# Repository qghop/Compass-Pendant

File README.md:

# Compass-Pendant
WIP - Creating a Pendant with LEDs and a Compass Module on a custom PCB

## Design Goals and Inspiration

The main design goal from the beginning was to create a unique piece of jewlery, from a Custom PCB with real-world functional components. 

Several purposes were ideated for this purpose. I initially wanted to create a GPS Logging Device to track my position, an idea I was first enamored by with [BOTW's Hero's Path Mode](https://www.youtube.com/watch?v=YSooSC6LfSU), and without giving my position data away to, or relying upon, a huge company like Google Maps' Timeline feature requires. I couldn't figure out a way to keep all the components small for this idea, so it was shelved, though I implemented a similar feature in my [Apple Photos Analysis Project](https://github.com/qghop/Apple-Photos-Analysis).

Different sensors, chips, and general designs were considered, but eventually using a Coin Cell Battery, an ATmega328P, and an I2C Magnetometer were chosen for ease of implementing, in both wiring and programming. 

The whole project was heavily inspired by the work of [Mitxela](https://mitxela.com/), especially his [UV Protection Amulet](https://www.youtube.com/watch?v=JhNMeJZ8Ll0) and [Fluid Simulation Pendant](https://www.youtube.com/watch?v=jis1MC5Tm8k). The header for chip programming was taken from the [KeyChainino](https://www.keychainino.com/) project, thanks to [upir](https://www.youtube.com/watch?v=Zsum_6dWfVU) for their video on the device. Additional thanks to the hundreds of KiCad tutorials used to build the PCB.

## Media

### V1

## V1 Successes

Honestly, I was suprised by how not difficult this project was. Obviously I have a very basic scope, but to have my PCB design work, essentially, first try, is remarkable as someone with only the base electrical experience required of a Mechanical Engineering grad. KiCad especially proved to be quite easy to learn.

A functional V1 device was created!

## V1 Failures

- A switch was initially considered, but was removed to more easily wire connections with the large battery pads taking most of the limited space. This was a mistake, a switch is really required for actual use. Removing the battery from the chosen holder is not easy, and a case for the PCB (which could hide the LEDs) would add a ton of complexity, and would cover up an, in my opinion, great looking bare PCB.

- The battery is oddly inconsistent in delivering power to the magnetometer. This problem needs to be properly diagnosed, but there is no issue in running the debug "BasicSpinningLights.ino" sketch, but there is sometimes issues with the Compass program loaded.

- PCBA is too expensive to justify for revisions, so V2 should be designed so I could assemble myself (mostly meaning larger components).

- The small, red LEDs aren't as appealing as envisioned. Could be fixed with a diffuser, a larger or variable resistor, or a cooler (blue, green) color.

- The snap-off header could be designed to be easier to cut off, or designed to be integrated into the jewlery, as say the part that connects to the necklace chain.

## Programming

I primarily referenced the [KeyChainino Guide](https://www.keychainino.com/how-to-program-keychainino-v144-via-isp/) for programming. Below is a summarized version, with some tweaks.

1. Install the MiniCore Library to the Arduino IDE.

2. Load the example sketch "ArduinoISP" to the Arduino UNO.

3. Remove the battery from the Pendant, and don't put it back in until finished. Physically connect the Pendant programming header to the proper pins of the UNO. 

    This can be done via wiring:

    Or via the ISP header of the UNO. The RESET pin of the ISP pins cannot be used though, so there must still be one manual connection to Digital Pin 10, acting as a digital reset:

4. Switch to the ATmega328 Board, with the following settings:

5. If first time programming the chip, run "Burn Bootloader" from Tools

6. Upload the sketch. If errors occour, wires are likely not connected properly. Tilting the pendant or the wires can help ensure connection.

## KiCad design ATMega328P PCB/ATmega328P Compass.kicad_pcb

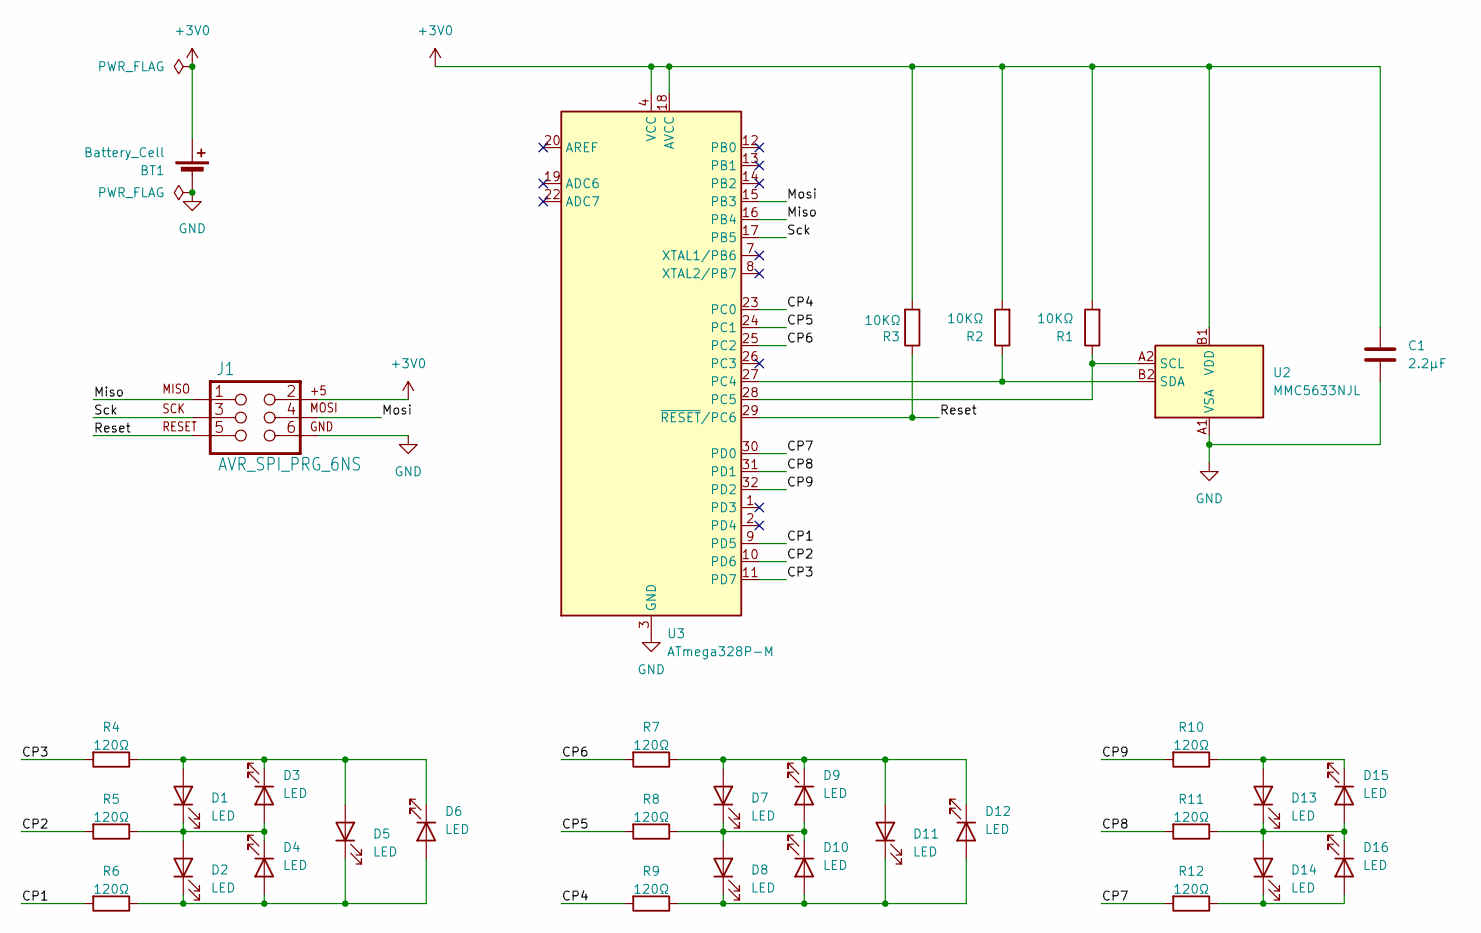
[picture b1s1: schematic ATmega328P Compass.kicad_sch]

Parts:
BT1: Battery_Cell; BatteryHolder_Keystone_3034_1x20mm
C1: 2.2µF; C_01005_0402Metric_Pad0.57x0.30mm_HandSolder
D1, D2, D3, D4, D5, D6, D7, D8, D9, D10, D11, D12, D13, D14, D15, D16: LED; LED_01005_0402Metric_Pad0.57x0.30mm_HandSolder
J1: AVR_SPI_PRG_6NS; 2X3-NS
R1, R2, R3: 10KΩ; R_0402_1005Metric_Pad0.72x0.64mm_HandSolder
R4, R5, R6, R7, R8, R9, R10, R11, R12: 120Ω; R_0402_1005Metric_Pad0.72x0.64mm_HandSolder
U2: MMC5633NJL; WLP-4_0.86x0.86mm_P0.4mm
U3: ATmega328P-M; QFN-32-1EP_5x5mm_P0.5mm_EP3.1x3.1mm

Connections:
+3V0: BT1.1 (+), C1.1, J1.2, R1.2, R2.2, R3.2, U2.B1 (VDD), U3.4 (VCC), U3.6 (VCC), U3.18 (AVCC)
/CP1: R6.2, U3.9 (PD5)
/CP2: R5.2, U3.10 (PD6)
/CP3: R4.2, U3.11 (PD7)
/CP4: R9.2, U3.23 (PC0)
/CP5: R8.2, U3.24 (PC1)
/CP6: R7.2, U3.25 (PC2)
/CP7: R12.2, U3.30 (PD0)
/CP8: R11.2, U3.31 (PD1)
/CP9: R10.2, U3.32 (PD2)
/Miso: J1.1, U3.16 (PB4)
/Mosi: J1.4, U3.15 (PB3)
/Reset: J1.5, R3.1, U3.29 (~RESET/PC6)
/Sck: J1.3, U3.17 (PB5)
GND: BT1.2 (-), C1.2, J1.6, U2.A1 (VSA), U3.3 (GND), U3.5 (GND), U3.21 (GND), U3.33 (GND)
unnamed: D1.2 (A), D3.1 (K), D5.2 (A), D6.1 (K), R4.1
unnamed: D1.1 (K), D2.2 (A), D3.2 (A), D4.1 (K), R5.1
unnamed: D2.1 (K), D4.2 (A), D5.1 (K), D6.2 (A), R6.1
unnamed: D8.1 (K), D10.2 (A), D11.1 (K), D12.2 (A), R9.1
unnamed: D7.1 (K), D8.2 (A), D9.2 (A), D10.1 (K), R8.1
unnamed: D7.2 (A), D9.1 (K), D11.2 (A), D12.1 (K), R7.1
unnamed: D13.2 (A), D15.1 (K), R10.1
unnamed: D13.1 (K), D14.2 (A), D15.2 (A), D16.1 (K), R11.1
unnamed: D14.1 (K), D16.2 (A), R12.1
unnamed: R1.1, U2.A2 (SCL), U3.28 (PC5)
unnamed: R2.1, U2.B2 (SDA), U3.27 (PC4)

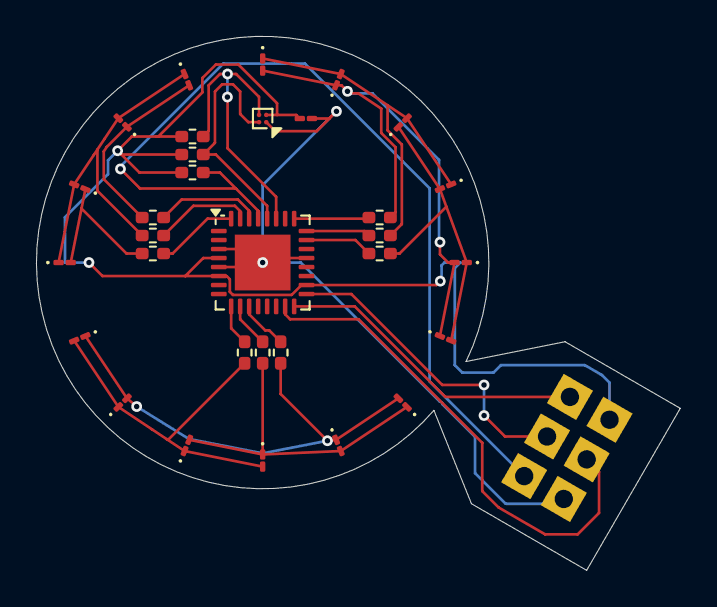
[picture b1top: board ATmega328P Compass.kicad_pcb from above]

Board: 2 copper layers, 35.8 x 29.7 mm, 33 parts (1 on the bottom side), 26 nets.

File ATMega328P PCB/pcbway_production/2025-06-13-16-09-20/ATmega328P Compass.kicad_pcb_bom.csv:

Designator,Quantity,Value,Footprint,Package,MPN,DNP,Mount_Type,Description,Sim.Pins
BT1,1,Battery_Cell,BatteryHolder_Keystone_3034_1x20mm,-,3034TR,,smt,Single-cell battery,
C1,1,2.2µF,C_01005_0402Metric_Pad0.57x0.30mm_HandSolder,0402,CL05A225MQ5NSNC,,smt,Unpolarized capacitor,
"D1, D10, D11, D12, D13, D14, D15, D16, D2, D3, D4, D5, D6, D7, D8, D9",16,LED,LED_01005_0402Metric_Pad0.57x0.30mm_HandSolder,0402,BL-HUB37A-AV-TRB,,smt,Light emitting diode,1=K 2=A
"R1, R2, R3",3,10KΩ,R_0402_1005Metric_Pad0.72x0.64mm_HandSolder,0402,0402WGF1002TCE,,smt,Resistor,
"R10, R11, R12, R4, R5, R6, R7, R8, R9",9,120Ω,R_0402_1005Metric_Pad0.72x0.64mm_HandSolder,0402,0402WGF1200TCE,,smt,Resistor,
U2,1,MMC5633NJL,WLP-4_0.86x0.86mm_P0.4mm,WLP-4(0.9x0.9),MMC5633NJL,,smt,"3-axis AMR Magnetometer, 30 G, I2C & I3C  Interface, 2mG RMS, WLP-4",
U3,1,ATmega328P-M,QFN-32-1EP_5x5mm_P0.5mm_EP3.1x3.1mm,VQFN-32_5x5,ATMEGA328P-MU,,smt,"20MHz, 32kB Flash, 2kB SRAM, 1kB EEPROM, QFN-32",

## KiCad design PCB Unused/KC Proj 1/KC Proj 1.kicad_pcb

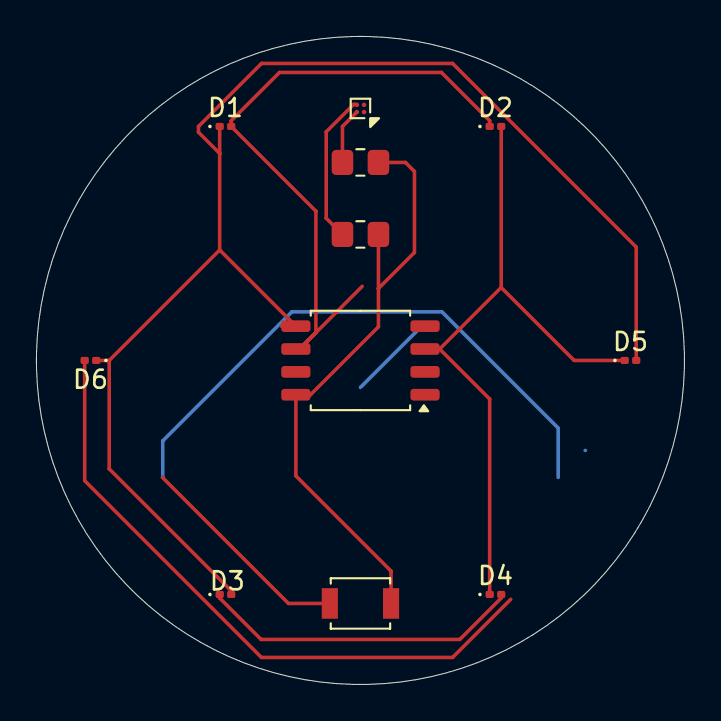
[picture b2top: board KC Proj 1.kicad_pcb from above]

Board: 2 copper layers, 36.0 x 36.0 mm, 12 parts (1 on the bottom side), 8 nets.

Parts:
BT1: Battery_Cell; BatteryHolder_Keystone_3034_1x20mm
D1, D2, D3, D4, D5, D6: LED; LED_0201_0603Metric
R1, R2: 10Kohm; R_0805_2012Metric_Pad1.20x1.40mm_HandSolder
SW1: SW_SPST; SW_SPST_B3U-1000P
U2: MMC5633NJL; WLP-4_0.86x0.86mm_P0.4mm
U3: ATtiny85-20S; SOIC-8_5.3x5.3mm_P1.27mm

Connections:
unnamed: BT1.1 (+), SW1.1 (A)
unnamed: BT1.2 (-), U2.A1 (VSA), U3.4 (GND)
unnamed: D1.2 (A), D2.1 (K), D3.1 (K), D4.2 (A), U3.6 (PB1)
unnamed: D1.1 (K), D3.2 (A), D5.2 (A), D6.1 (K), U3.5 (AREF/PB0)
unnamed: D2.2 (A), D4.1 (K), D5.1 (K), D6.2 (A), U3.3 (XTAL2/PB4)
unnamed: R1.2, R2.2, SW1.2 (B), U2.B1 (VDD), U3.8 (VCC)
unnamed: R1.1, U2.A2 (SCL), U3.7 (PB2)
unnamed: R2.1, U2.B2 (SDA), U3.2 (XTAL1/PB3)

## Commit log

2025-06-14 Uploading PCB 1
    Uploading ATMega328P PCB (First PCB sent to PCBWay) and previous attempts/ideas with ATTiny85+84
2025-06-15 Added v1 Images
2025-07-08 Basic LED control code
2025-07-09 Minor edits for viewing
2025-07-09 Added media, code from working device
2025-07-09 Revamped Readme
2025-07-09 Added videos to README
